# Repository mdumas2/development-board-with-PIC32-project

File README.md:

# PCB project of our development board utilizing PIC32
***
## SCHEMATICS

## 2D

## 3D

## ISSUES

# Code of our development board utilizing PIC32
***
## STATE MACHINE

## UML DIAGRAM

## Bluetooth App

## VS code App

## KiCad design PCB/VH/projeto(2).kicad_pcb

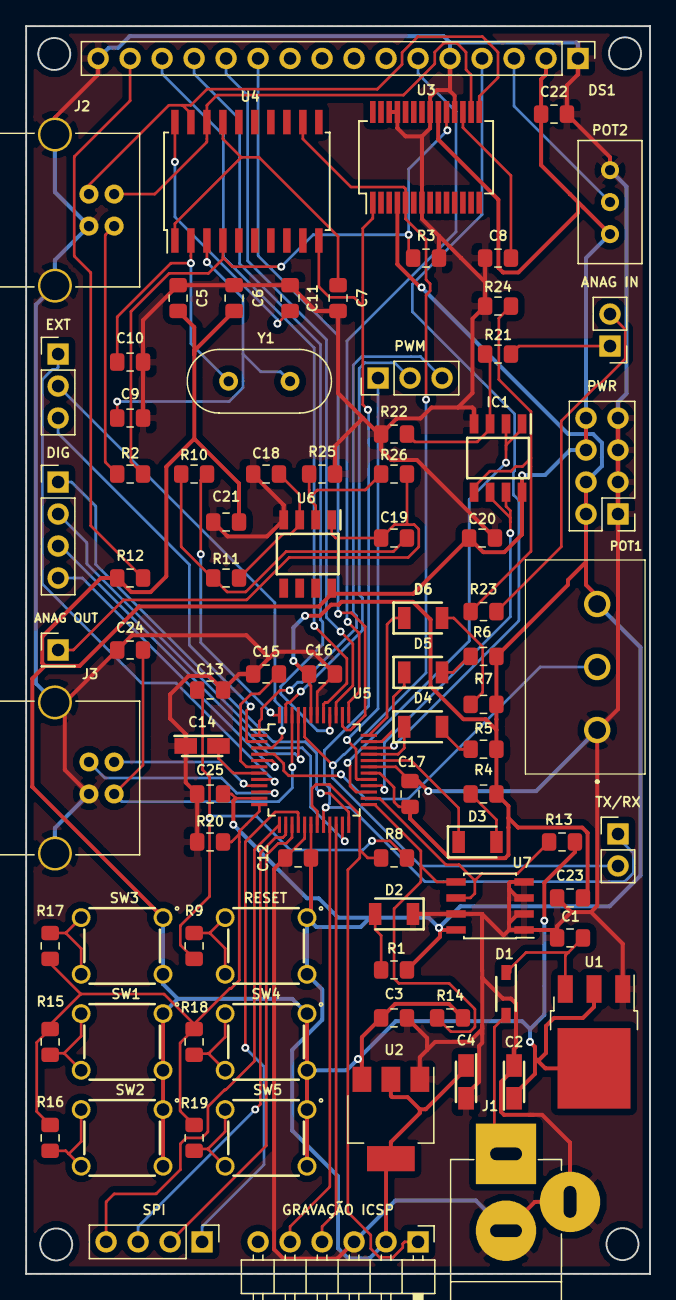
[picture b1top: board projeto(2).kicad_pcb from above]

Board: 2 copper layers, 49.5 x 99.1 mm, 87 parts (0 on the bottom side), 77 nets.

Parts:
ANAG IN: Entrada Anag; PinHeader_1x02_P2.54mm_Vertical
ANAG OUT: Saída Anag; PinHeader_1x01_P2.54mm_Vertical
C1, C3, C5, C6, C7, C8, C11, C12, C13, C15, C16, C17, C20, C21, C22, C23, C25: 100nF; C_0805_2012Metric_Pad1.15x1.40mm_HandSolder
C2, C4, C14: 10uF; CAPPM3216X180N
C9, C10: 22pF; C_0805_2012Metric_Pad1.15x1.40mm_HandSolder
C18, C19, C24: 10nF; C_0805_2012Metric_Pad1.15x1.40mm_HandSolder
D1: D_Schottky; SOD3716X145N
D2: LED; LEDC3216X120N
D3, D4, D5, D6: .; LEDC3216X120N
DIG: Digitais; PinHeader_1x04_P2.54mm_Vertical
DS1: JHD162A; Socket_Strip_Straight_1x16_Pitch2.54mm
EXT: EXT; PinHeader_1x03_P2.54mm_Vertical
GRAVAÇÃO ICSP: Gravação; PinHeader_1x06_P2.54mm_Horizontal
IC1: LM358DG; SOIC127P600X175-8N
J1: Jack-DC; JACK_ALIM
J2: USB_B
J3: USB_B2; USB_B
POT1: 10k; P160KN0QD15B10K
POT2: 10k; Potentiometer_Bourns_3296W_Vertical
PWM: PWM; PinHeader_1x03_P2.54mm_Vertical
PWR: PWR; PinHeader_2x04_P2.54mm_Vertical
R1, R4, R5, R6, R7: 330; R_0805_2012Metric_Pad1.15x1.40mm_HandSolder
R2: 4.7k; R_0805_2012Metric_Pad1.15x1.40mm_HandSolder
R3, R9, R13, R14: 10k; R_0805_2012Metric_Pad1.15x1.40mm_HandSolder
R8, R17, R20: 1k; R_0805_2012Metric_Pad1.15x1.40mm_HandSolder
R10, R11: 3.3k; R_0805_2012Metric_Pad1.15x1.40mm_HandSolder
R12, R18, R21, R23: 470; R_0805_2012Metric_Pad1.15x1.40mm_HandSolder
R15: 6.8k; R_0805_2012Metric_Pad1.15x1.40mm_HandSolder
R16: 3,3k; R_0805_2012Metric_Pad1.15x1.40mm_HandSolder
R19: 100; R_0805_2012Metric_Pad1.15x1.40mm_HandSolder
R22, R24: 910; R_0805_2012Metric_Pad1.15x1.40mm_HandSolder
R25: 9,1k; R_0805_2012Metric_Pad1.15x1.40mm_HandSolder
R26: 4,7k; R_0805_2012Metric_Pad1.15x1.40mm_HandSolder
RESET: 1825910-6
SPI: SPI; PinHeader_1x04_P2.54mm_Vertical
SW1, SW2, SW3, SW4, SW5: 1825910-6
TX/RX: Conn_01x02; PinHeader_1x02_P2.54mm_Vertical
U1: LD1117DT50TR; TO-252-3_TabPin2
U2: LD1117S33TR_SOT223; SOT-223-3_TabPin2
U3: FT232RL; SSOP-28_5.3x10.2mm_Pitch0.65mm
U4: MCP2200-I-SO; SOIC-20W_7.5x12.8mm_P1.27mm
U5: PIC/MICRO; TQFP-48_7x7mm_P0.5mm
U6: LM358; SOIC127P600X175-8N
U7: 24LC512; SOIC-8_3.9x4.9mm_P1.27mm
Y1: 12MHz; Crystal_HC49-4H_Vertical

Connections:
/3.3V: C4.1, C12.2, C16.2, C17.2, C23.2, C25.1, GRAVAÇÃO ICSP.2, POT1.3, PWR.2, PWR.4, R1.1, R4.2, R5.2, R6.1, R7.1, RESET.1, RESET.2, U2.2, U3.4, U5.11, U5.18, U5.30, U5.43, U7.8
/5V: C2.1, C3.1, C5.1, C6.1, C20.1, C21.2, C22.1, DS1.2, IC1.8, POT2.3, PWR.6, PWR.8, R12.2, R13.1, R14.1, SW1.1, SW1.2, SW2.1, SW2.2, SW3.1, SW3.2, SW4.1, SW4.2, SW5.1, SW5.2, U1.2, U2.3, U3.20, U6.8
/Comunicação/3.3v: C7.1, U4.1, U4.17
/Comunicação/RST: R2.2, R3.1, U3.19, U4.4
/Comunicação/RX: TX/RX.2, U3.5, U4.12, U5.44
/Interface/EN1: ANAG IN.1, R21.1
/Interface/EN2: ANAG IN.2, R23.1
/Interface/IN1: IC1.1, IC1.2, U5.27
/Interface/IN2: IC1.6, IC1.7, U5.28
/Interface/IN3: POT1.2, U5.4
/Interface/PWM: R10.2, U5.48
/Interface/SaidaANA: ANAG OUT.1, C19.1, R26.1, U6.1
/Periféricos/E: DS1.6, U5.37
/Periféricos/LCD1: DS1.11, U5.38
/Periféricos/LCD2: DS1.12, U5.39
/Periféricos/LCD3: DS1.13, U5.40
/Periféricos/LCD4: DS1.14, U5.41
/Periféricos/RS: DS1.4, U5.34
/Periféricos/SCL: R13.2, U5.26, U7.6
/Periféricos/SDA: R14.2, U5.25, U7.5
/Periféricos/TECLADO: R15.2, R16.2, R17.2, R18.2, R19.2, R20.2, U5.12
/microcontrolador/MCLR: GRAVAÇÃO ICSP.1, R8.2, U5.19
/microcontrolador/PGEC1: DIG.1, U5.24
/microcontrolador/PGEC2: GRAVAÇÃO ICSP.5, U5.21
/microcontrolador/PGEC3: DIG.4, U5.5
/microcontrolador/PGED1: DIG.2, U5.23
/microcontrolador/PGED2: GRAVAÇÃO ICSP.4, U5.22
/microcontrolador/PGED3: DIG.3, U5.45
/microcontrolador/PWM2: PWM.3, U5.1
/microcontrolador/PWM3: PWM.2, U5.47
/microcontrolador/PWM4: PWM.1, U5.29
/microcontrolador/RX: TX/RX.1, U3.1, U4.10, U5.20
GND: C1.2, C2.2, C3.2, C4.2, C5.2, C6.2, C7.2, C8.2, C9.2, C10.1, C11.1, C12.1, C13.2, C14.1, C15.2, C16.1, C17.1, C18.1, C20.2, C21.1, C22.2, C23.1, C24.2, C25.2, D2.1, DS1.1, DS1.5, DS1.16, GRAVAÇÃO ICSP.3, IC1.4, J1.2, J1.3, J2.4, J2.5, J3.4, J3.5, POT1.1, POT2.1, PWR.1, PWR.3, PWR.5, PWR.7, R3.2, R20.1, R22.2, R24.2, R25.2, U1.1, U2.1, U3.7, U3.18, U3.21, U3.25, U3.26, U5.17, U5.31, U5.42, U6.4, U7.1, U7.2, U7.3, U7.4, U7.7
unnamed: C1.1, D1.1, U1.3
unnamed: C8.1, U3.17
unnamed: C9.1, U4.3, Y1.1
unnamed: C10.2, U4.2, Y1.2
unnamed: C11.2, U4.20
unnamed: C13.1, R8.1, R9.1
unnamed: C14.2, U5.7
unnamed: C15.1, U5.6
unnamed: C18.2, R11.1, U6.3
unnamed: C19.2, R10.1, R11.2
unnamed: C24.1, J3.1, U5.46
unnamed: D1.2, J1.1
unnamed: D2.2, R1.2
unnamed: D3.1, U5.32
unnamed: D3.2, R4.1
unnamed: D4.1, U5.33
unnamed: D4.2, R5.1
unnamed: D5.1, U5.35
unnamed: D5.2, R6.2
unnamed: D6.1, U5.36
unnamed: D6.2, R7.2
unnamed: DS1.3, POT2.2
unnamed: DS1.15, R12.1
unnamed: IC1.3, R21.2, R22.1
unnamed: IC1.5, R23.2, R24.1
unnamed: J2.1, R2.1
unnamed: J2.2, U3.16, U4.18
unnamed: J2.3, U3.15, U4.19
unnamed: J3.2, U5.9
unnamed: J3.3, U5.10
unnamed: SPI.1, U5.16
unnamed: SPI.2, U5.15
unnamed: SPI.3, U5.14
unnamed: SPI.4, U5.13
unnamed: EXT.1, U5.8
unnamed: EXT.2, U5.3
unnamed: EXT.3, U5.2
unnamed: R9.2, RESET.3, RESET.4
unnamed: R15.1, SW1.3, SW1.4
unnamed: R16.1, SW2.3, SW2.4
unnamed: R17.1, SW3.3, SW3.4
unnamed: R18.1, SW4.3, SW4.4
unnamed: R19.1, SW5.3, SW5.4
unnamed: R25.1, R26.2, U6.2

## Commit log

2020-07-23 PCB and Code
2020-07-24 Documetation
